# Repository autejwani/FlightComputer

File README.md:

# Flight Computer Firmware

This repository contains the **C++ firmware** and hardware design files for a custom **rocket flight computer** built around a Teensy development kit. The system is designed for my L1 model rocket and emphasizes low-level control and modular sensor drivers.

All firmware is written **from scratch in C++**, with no high-level sensor abstraction libraries, to allow full control over hardware configuration, timing, and data flow.

---

## System Overview

The flight computer integrates multiple sensing, estimation, and communication subsystems to estimate vehicle state and transmit telemetry during flight.

The current implementation focuses on:
- **Altitude estimation using an Extended Kalman Filter (EKF)**
- **Low-level sensor interfacing over I2C**
- **LoRa-based telemetry**
- **Modular and scalable firmware architecture**

---

## Project Structure

```text

├── Controls/
│   ├── ekf.cpp
│   └── ekf.h
│
├── Sensing/
│   ├── imu.cpp
│   ├── imu.h
│   ├── baro.cpp
│   ├── baro.h
│   ├── mag.cpp
│   └── mag.h
│
├── Utilities/
│   ├── i2c.cpp
│   └── i2c.h
│
├── LoRa/
│   ├── transmitter.cpp
│   └── receiver.cpp
│
└── main.cpp
```
## Folder Descriptions

### **Controls**
Contains control and estimation algorithms.

- **`ekf.cpp / ekf.h`**  
  Implements an **Extended Kalman Filter (EKF)** used to estimate the vehicle’s **Z-axis state (altitude)** during flight.  
  The EKF fuses inertial and barometric measurements and is designed to be expanded to full **3-axis state estimation**.

---

### **Sensing**
Contains low-level sensor drivers, each split into a header and implementation file.

- **IMU (`imu.cpp / imu.h`)**  
  Provides accelerometer and gyroscope data for motion sensing.

- **Barometer (`baro.cpp / baro.h`)**  
  Provides pressure-based altitude measurements used by the EKF.

All sensors are configured and read at the **register level**, without relying on vendor abstraction libraries.

---

### **Utilities**
Contains reusable hardware communication helpers.

- **I2C (`i2c.cpp / i2c.h`)**  
  Implements low-level I2C read/write utilities, multi-byte transactions, and device probing.  
  This layer is shared across all sensor drivers.

---

## **LoRa**
Contains long-range wireless communication code used for flight telemetry and ground station reception.

The LoRa subsystem is designed to transmit **compact, fixed-length binary packets** for reliability, low latency, and ease of parsing on resource-constrained hardware.

---

### **Telemetry Packet Format**

Each LoRa transmission consists of a **fixed 11-byte packet** with the following structure:

| Byte Index | Field       | Size (bytes) | Type      | Description |
|-----------:|-------------|--------------|-----------|-------------|
| 0          | Packet ID   | 1            | `uint8_t` | Reserved for packet type / sync|
| 1–4        | Timestamp   | 4            | `uint32_t`| System timestamp in **milliseconds** |
| 5–6        | Temperature | 2            | `int16_t` | Temperature in **°C × 100** (fixed-point) |
| 7–10       | Pressure    | 4            | `int32_t` | Pressure in **Pascals (Pa)** |

**Total packet size:** `11 bytes`

---

### **Encoding Details**

- **Timestamp**
  - Big-endian format
  - Represents system uptime in milliseconds
  - Used for packet ordering and time correlation

- **Temperature**
  - Signed 16-bit fixed-point value  
  - Conversion:  
    ```
    temperature (°C) = int16_value / 100.0
    ```
  - Example: `2534 → 25.34 °C`

- **Pressure**
  - Signed 32-bit integer
  - Units: **Pascals (Pa)**
  - Intended for altitude calculation and EKF validation on the ground station

---

### **`transmitter.cpp`**
Packages sensor telemetry into the fixed 11-byte binary packet and transmits it over LoRa at **915 MHz**.

Responsibilities include:
- Packing sensor values into fixed-point binary fields
- Enforcing a fixed packet length
- Periodic telemetry transmission during flight

The packet structure is intentionally minimal to:
- Reduce airtime
- Improve link reliability
- Avoid dynamic memory allocation

---

### **`receiver.cpp`**
Receives and validates incoming LoRa packets on the ground station.

Responsibilities include:
- Verifying packet length (`11 bytes`)
- Parsing binary fields into native types
- Converting fixed-point values to floating-point
- Displaying telemetry via **Serial** and **OLED**

Packets with unexpected lengths are discarded to ensure data integrity.

---

### **Design**
Contains the hardware design files for the flight computer PCB.

This includes:
- PCB layout files  
- Schematics  
- Manufacturing and fabrication outputs  

These files document the **complete electrical design** of the flight computer hardware.

---

## `main.cpp`

`main.cpp` serves as the system entry point and integrates all subsystems. It:

- Initializes I2C and sensors  
- Initializes the EKF  
- Continuously reads sensor data  
- Runs the EKF update loop  
- Monitors the **Z-axis (altitude) state estimate** in real time  
- Interfaces with the LoRa telemetry system  

---

## Design Goals

- C++ firmware for embedded flight systems  
- Register-level sensor control  
- Clear separation between sensing, utilities, control, and communication  
- EKF-based state estimation  
- Reliable long-range telemetry  
- Scalable architecture for future expansion  

---

## Build Environment

- **Language:** C++  
- **Framework:** Arduino (STM32 core)  
- **Build System:** PlatformIO  
- **Target:** Custom STM32-based flight computer hardware

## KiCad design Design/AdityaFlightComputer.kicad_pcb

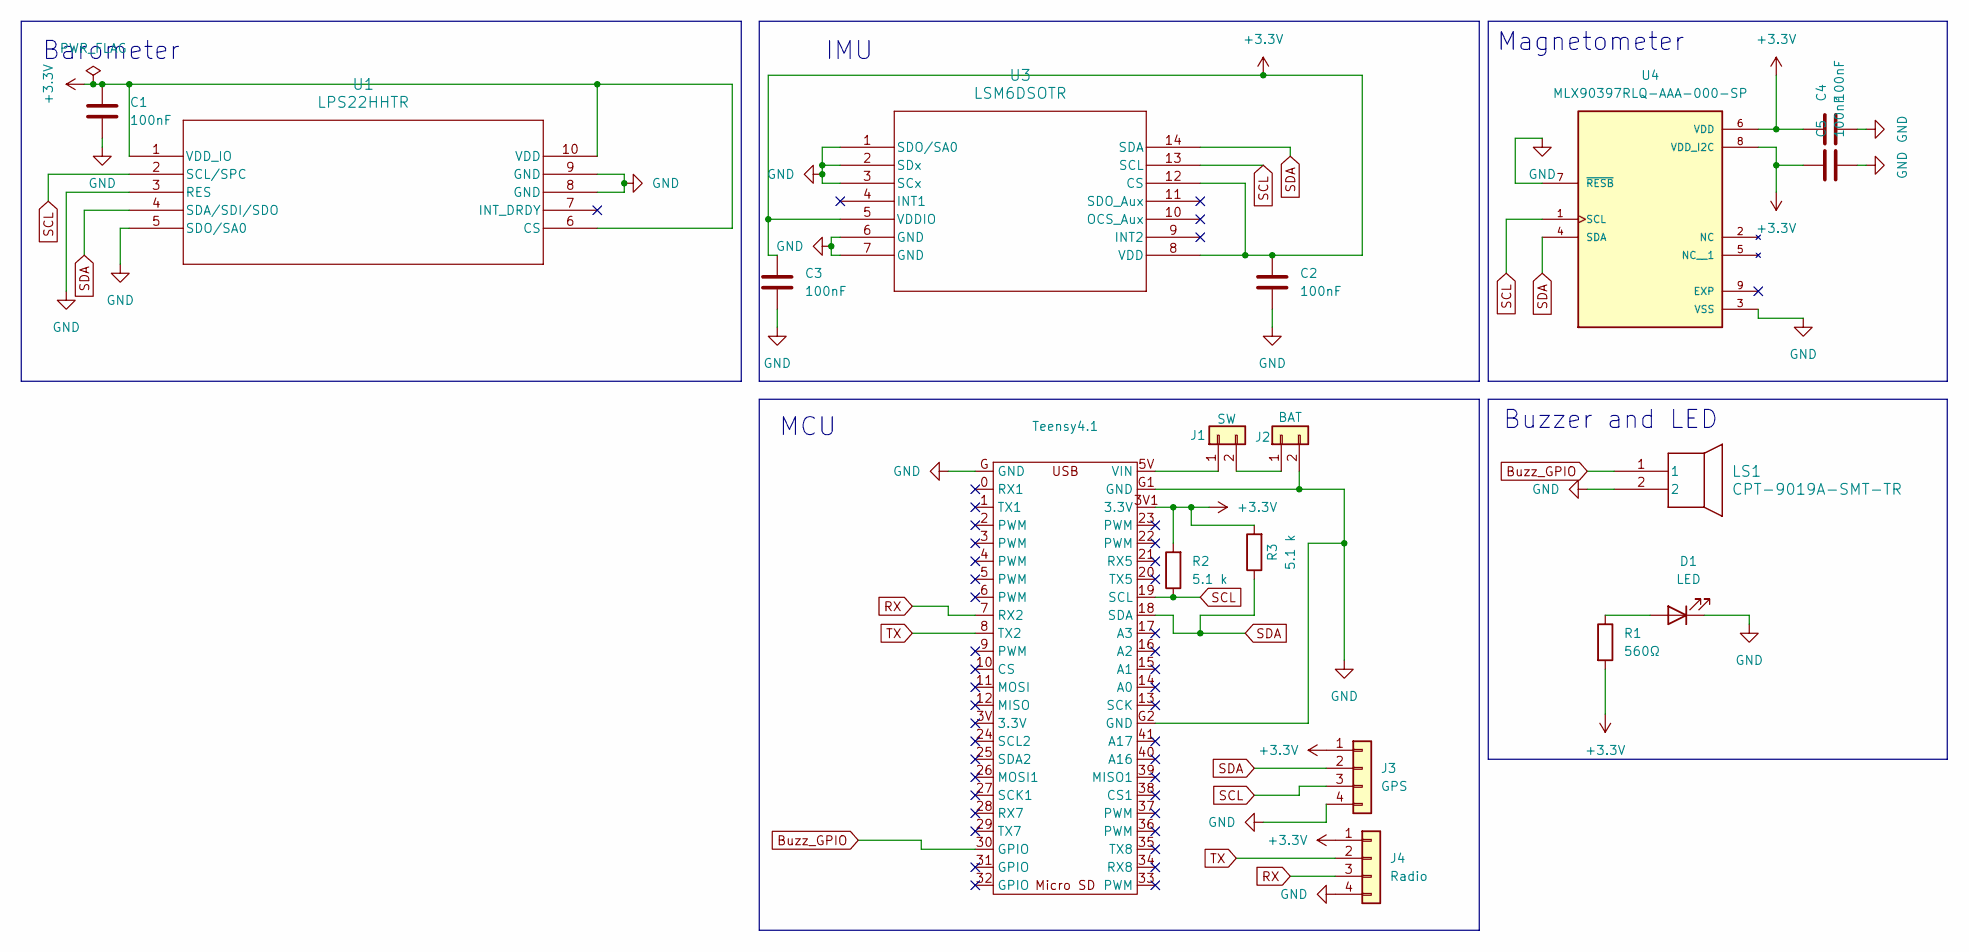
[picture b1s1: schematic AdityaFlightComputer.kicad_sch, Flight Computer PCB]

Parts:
C1, C2, C3, C4, C5: 100nF; C_0603_1608Metric
D1: LED; LED_0805_2012Metric
J1: SW; JST_XH_S2B-XH-A-1_1x02_P2.50mm_Horizontal
J2: BAT; JST_XH_S2B-XH-A-1_1x02_P2.50mm_Horizontal
J3: GPS; JST_XH_S4B-XH-A-1_1x04_P2.50mm_Horizontal
J4: Radio; JST_XH_S4B-XH-A-1_1x04_P2.50mm_Horizontal
LS1: CPT-9019A-SMT-TR; Adafruit_Buzzer
R1: 560Ω; R_0603_1608Metric
R2, R3: 5.1 k; R_0603_1608Metric
Teensy4.1: teensy
U1: LPS22HHTR; HLGA-10L_2X2X0P73_STM
U3: LSM6DSOTR; LGA-14L_2P5X3X0P86_STM
U4: MLX90397RLQ-AAA-000-SP; SON40P200X250X40-9N; PARTREV 002

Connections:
+3.3V: C1.1, C2.1, C3.1, C4.1, C5.1, J3.1, J4.1, R1.2, R2.2, R3.2, Teensy4.1.3V1 (3.3V), U1.1 (VDD_IO), U1.6 (CS), U1.10 (VDD), U3.5 (VDDIO), U3.8 (VDD), U3.12 (CS), U4.6 (VDD), U4.8 (VDD_I2C)
Buzz_GPIO: LS1.1, Teensy4.1.30 (GPIO)
GND: C1.2, C2.2, C3.2, C4.2, C5.2, D1.1 (K), J2.2, J3.4, J4.4, LS1.2, Teensy4.1.G (GND), Teensy4.1.G1 (GND), Teensy4.1.G2 (GND), U1.3 (RES), U1.5 (SDO/SA0), U1.8 (GND), U1.9 (GND), U3.1 (SDO/SA0), U3.2 (SDx), U3.3 (SCx), U3.6 (GND), U3.7 (GND), U4.3 (VSS), U4.7 (~RESB)
unnamed: D1.2 (A), R1.1
unnamed: J1.1, Teensy4.1.5V (VIN)
unnamed: J1.2, J2.1
RX: J4.3, Teensy4.1.7 (RX2)
SCL: J3.3, R2.1, Teensy4.1.19 (SCL), U1.2 (SCL/SPC), U3.13 (SCL), U4.1 (SCL)
SDA: J3.2, R3.1, Teensy4.1.18 (SDA), U1.4 (SDA/SDI/SDO), U3.14 (SDA), U4.4 (SDA)
TX: J4.2, Teensy4.1.8 (TX2)

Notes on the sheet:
Buzzer and LED
MCU
Magnetometer
IMU
Barometer

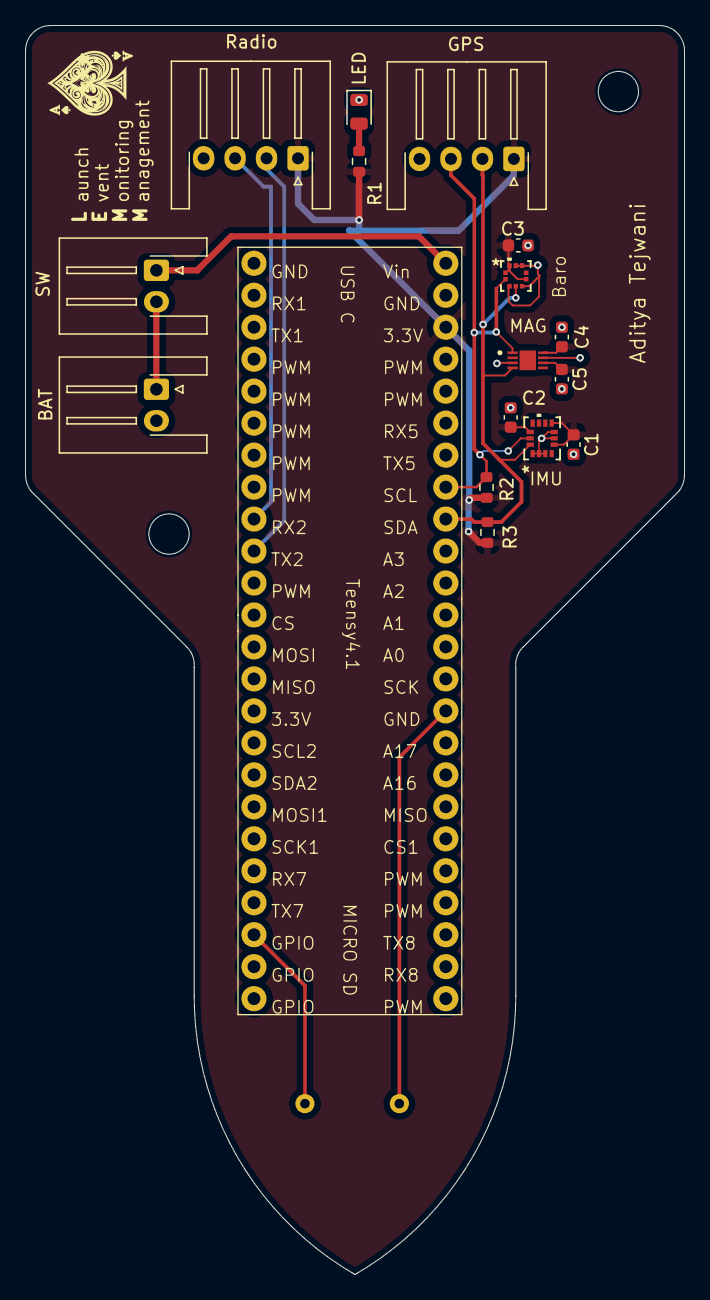
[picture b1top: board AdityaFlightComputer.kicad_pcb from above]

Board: 2 copper layers, 52.4 x 99.2 mm, 18 parts (1 on the bottom side), 10 nets.
